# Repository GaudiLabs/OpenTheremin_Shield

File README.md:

## Open.Theremin.UNO hardware description 

Schematics, printed circuit board (PCB) design, bill of materials (BOM) for the Open.Theremin.UNO arduino shield.
For software see separate git repository.

### Don't click on the files!
Click on the "Download ZIP" Button to the right or [Click here](https://github.com/GaudiLabs/OpenTheremin_Shield/archive/master.zip) 
Then unpack the archive.

### Open Source Theremin based on the Arduino Platform

Open.Theremin.UNO is an arduino shield to build the legendary music instrument invented by Leon Theremin back in 1920. The theremin is played with two antennas, one to control the pitch and one for volume. The electronic shield with two ports to connect those antennas comprises two heterodyne oscillators to measure the distance of the hand to the antenna when playing the instrument. The resulting signal is fed into the arduino. After linearization and filtering the arduino generates the instruments sound that is then played through a high quality digital analog audio converter on the board. The characteristics of the sound can be determined by a wave table on the arduino.

For more info on the open source project and on availability of ready made shield see:

http://www.gaudi.ch/OpenTheremin/

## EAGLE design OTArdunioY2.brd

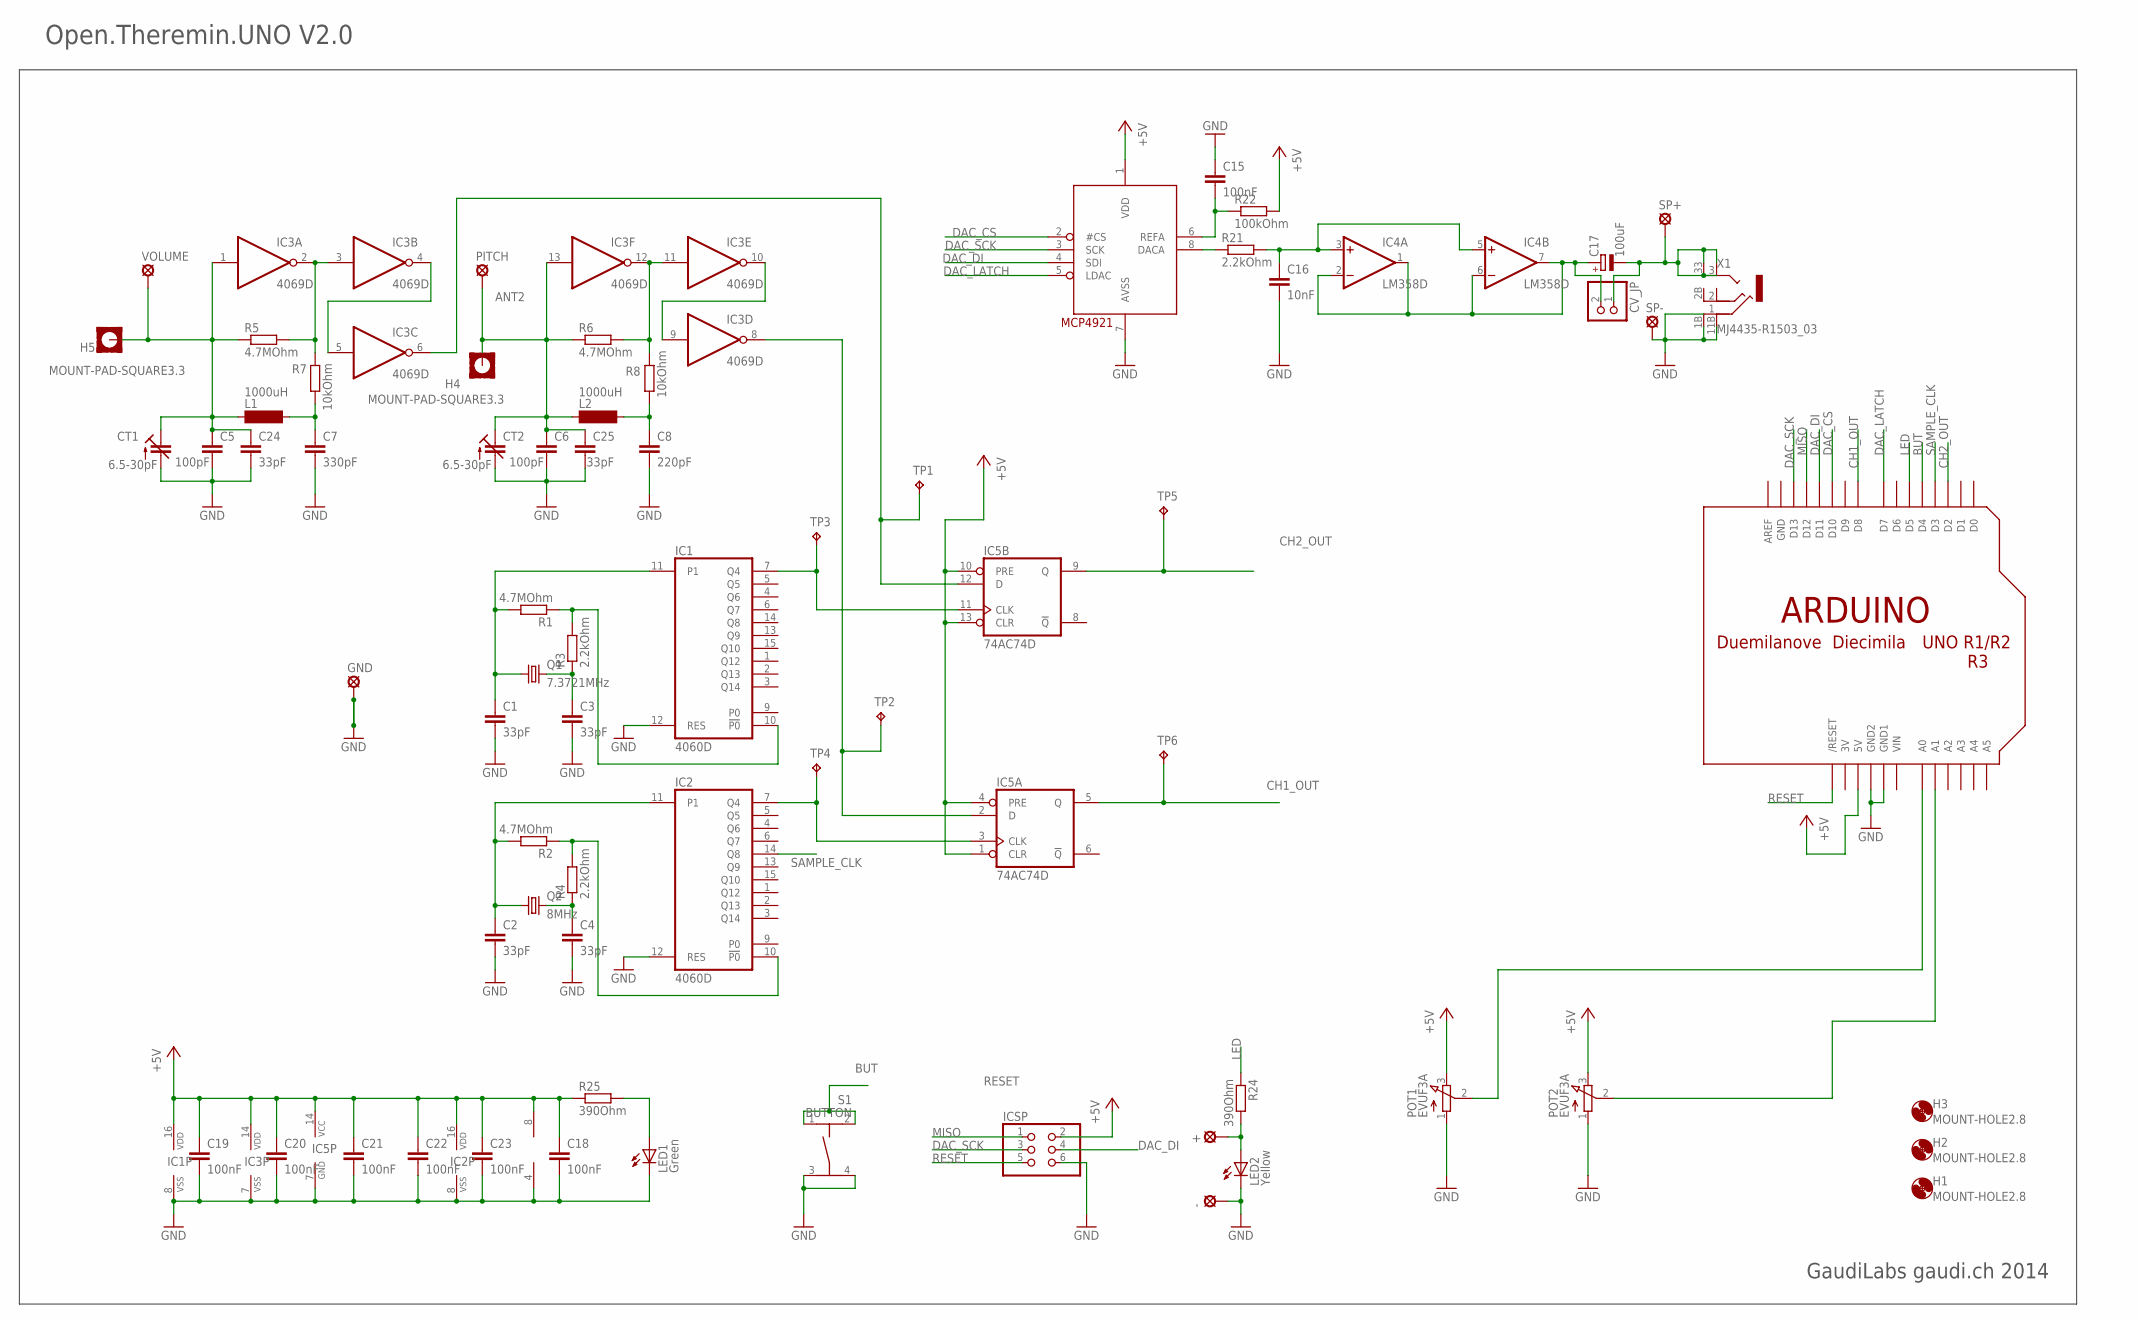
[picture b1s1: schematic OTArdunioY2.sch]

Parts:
+: LSP11
-: LSP11
C1, C2, C3, C4, C24, C25: 33pF; C0805
C5, C6: 100pF; C0805
C7: 330pF; C0805
C8: 220pF; C0805
C15, C18, C19, C20, C21, C22, C23: 100nF; C0805
C16: 10nF; C0805
C17: 100uF; 153CLV-0505
CT1, CT2: 6.5-30pF; CTRIMTZBX4
CV_JP: PINHD-1X2; 1X02
GND: SE14
H1, H2, H3: MOUNT-HOLE2.8; 3,3
H4, H5: MOUNT-PAD-SQUARE3.3; 3,3-PAD-SQUARE
IC1, IC2: 4060D; SO16
IC3: 4069D; SO14
IC4: LM358D; SO08
IC5: 74AC74D; SO14
IC6: MCP4921SO8; SO08
ICSP: PINHD-2X3; 2X03
L1, L2: 1000uH; MS42
LED1: Green; CHIPLED_0805
LED2: Yellow; CHIPLED_0805
PITCH: SE14
POT1, POT2: EVUF3A; EVUF
Q1: 7.3721MHz; CSM-7X-DU
Q2: 8MHz; CSM-7X-DU
R1, R2, R5, R6: 4.7MOhm; M0805
R3, R4, R21: 2.2kOhm; M0805
R7, R8: 10kOhm; M0805
R22: 100kOhm; M0805
R24, R25: 390Ohm; M0805
S1: BUTTON; TASTER-9314_SMD
SP+: LSP11
SP-: LSP11
TP1, TP2, TP3, TP4, TP5, TP6: TPTP15R; TP15R
U$1: ARDUINODUEMILANOVE-NODIM; ARDUINO-NODIM
VOLUME: SE14
X1: MJ4435-R1503_03; 1503_02

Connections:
3V: U$1.3V
+5V: C18.1, C19.1, C20.1, C21.1, C22.1, C23.1, IC1.16 (VDD), IC2.16 (VDD), IC3.14 (VDD), IC4.8 (V+), IC5.1 (CLR), IC5.4 (PRE), IC5.10 (PRE), IC5.13 (CLR), IC5.14 (VCC), IC6.1 (VDD), ICSP.2, POT1.3 (E), POT2.3 (E), R22.2, R25.1, U$1.5V
ANT2: C6.1, C25.1, CT2.1 (E), H4.B3,3, IC3.13 (I), L2.1, PITCH.MP, R6.1
BUT: S1.1, S1.2, U$1.D4
CH1_OUT: IC5.5 (Q), TP6.TP, U$1.D8
CH2_OUT: IC5.9 (Q), TP5.TP, U$1.D2
DAC_CS: IC6.2 (#CS), U$1.D10
DAC_DI: IC6.4 (SDI), ICSP.4, U$1.D11
DAC_LATCH: IC6.5 (LDAC), U$1.D7
DAC_SCK: IC6.3 (SCK), ICSP.3, U$1.D13
GND: -.MP, C1.2, C2.2, C3.2, C4.2, C5.2, C6.2, C7.2, C8.2, C15.1, C16.2, C18.2, C19.2, C20.2, C21.2, C22.2, C23.2, C24.2, C25.2, CT1.2 (A), CT2.2 (A), GND.MP, IC1.8 (VSS), IC1.12 (RES), IC2.8 (VSS), IC2.12 (RES), IC3.7 (VSS), IC4.4 (V-), IC5.7 (GND), IC6.7 (AVSS), ICSP.6, LED1.C, LED2.C, POT1.1 (A), POT2.1 (A), S1.3, S1.4, SP-.MP, U$1.GND, U$1.GND1, U$1.GND2, X1.1 (1_1), X1.1B (1_3), X1.11B (1_4)
LED: R24.1, U$1.D5
MISO: ICSP.1, U$1.D12
unnamed: C1.1, IC1.11 (P1), Q1.1, R1.2
unnamed: C17.-, CV_JP.1, SP+.MP, X1.3 (3_1), X1.3B (3_2), X1.33 (3_3), X1.33B (3_4)
unnamed: IC1.10 (!P0), R1.1, R3.2
unnamed: POT2.2 (S), U$1.A1
unnamed: +.MP, LED2.A, R24.2
unnamed: C3.1, Q1.2, R3.1
unnamed: C2.1, IC2.11 (P1), Q2.1, R2.2
unnamed: LED1.A, R25.2
unnamed: C4.1, Q2.2, R4.1
unnamed: IC2.10 (!P0), R2.1, R4.2
unnamed: C5.1, C24.1, CT1.1 (E), H5.B3,3, IC3.1 (I), L1.1, R5.1, VOLUME.MP
unnamed: IC3.6 (O), IC5.12 (D), TP1.TP
unnamed: C7.1, L1.2, R7.1
unnamed: POT1.2 (S), U$1.A0
unnamed: C17.+, CV_JP.2, IC4.1 (OUT), IC4.2 (-IN), IC4.6 (-IN), IC4.7 (OUT)
unnamed: IC3.8 (O), IC5.2 (D), TP2.TP
unnamed: C8.1, L2.2, R8.1
unnamed: IC1.7 (Q4), IC5.11 (CLK), TP3.TP
unnamed: IC2.7 (Q4), IC5.3 (CLK), TP4.TP
unnamed: C15.2, IC6.6 (REFA), R22.1
unnamed: IC6.8 (DACA), R21.1
unnamed: IC3.11 (I), IC3.12 (O), R6.2, R8.2
unnamed: IC3.2 (O), IC3.3 (I), R5.2, R7.2
unnamed: IC3.4 (O), IC3.5 (I)
unnamed: C16.1, IC4.3 (+IN), IC4.5 (+IN), R21.2
unnamed: IC3.9 (I), IC3.10 (O)
RESET: ICSP.5, U$1.RESET (/RESET)
SAMPLE_CLK: IC2.14 (Q8), U$1.D3
VIN: U$1.VIN

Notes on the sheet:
RESET
Open.Theremin.UNO V2.0
GaudiLabs gaudi.ch 2014

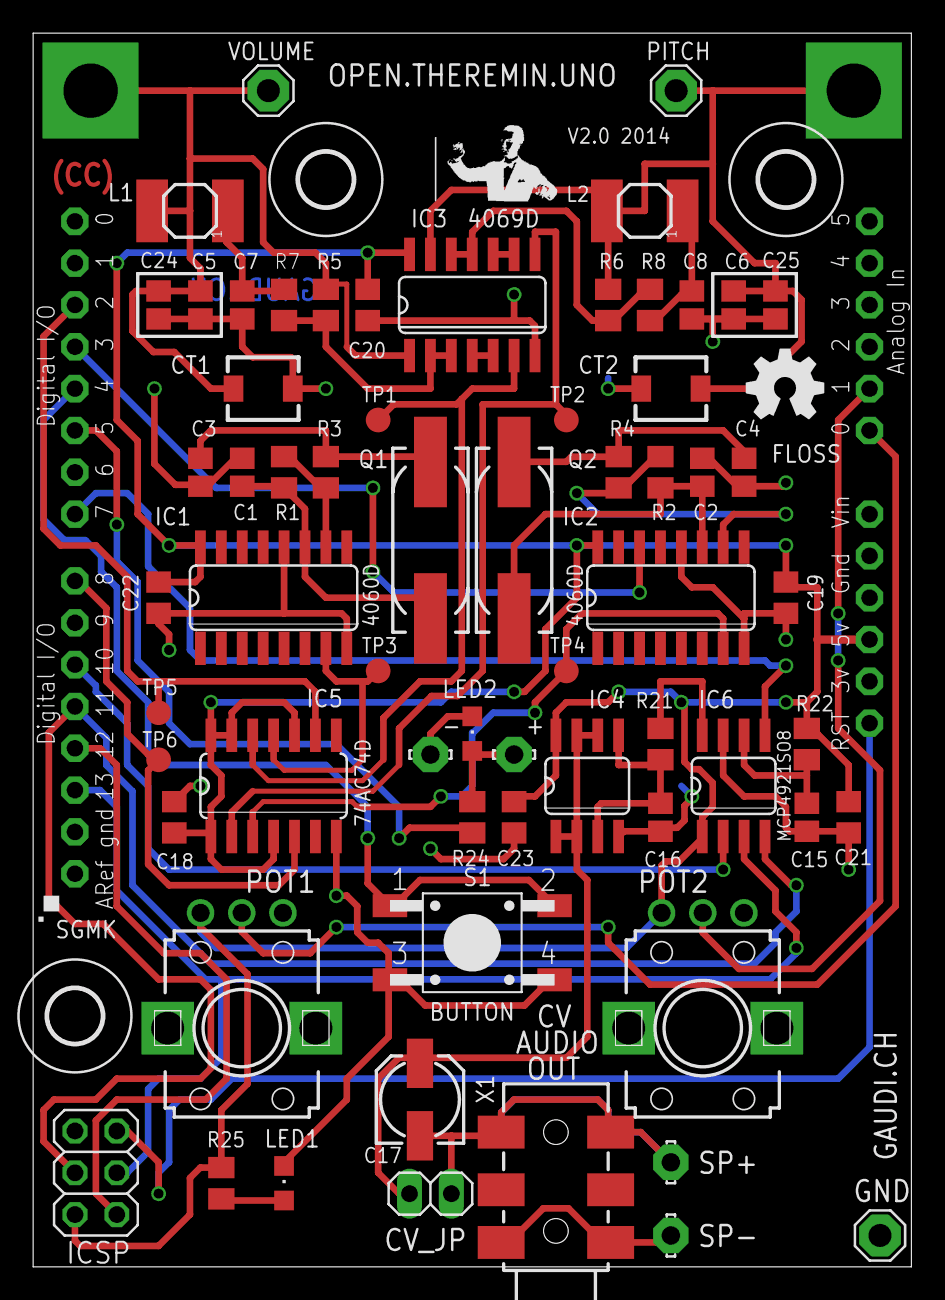
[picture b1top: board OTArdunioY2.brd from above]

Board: 4 copper layers, 53.3 x 74.9 mm, 70 parts (0 on the bottom side), 40 nets.

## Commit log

2014-10-29 Version 2.0 - first batch design
2014-10-29 GNU License Version 3
2014-10-29 Version 2.0
2015-06-12 Updated the bill of materials
2015-06-12 Updated the Bill of Materials (BOM)
2015-06-12 Updated the Bill of Materials (BOM) with new coil.
2016-02-22 Added Mechanical Drawings
    for Antenna and extension Parts
2016-03-23 updated BOM with digikey parts
